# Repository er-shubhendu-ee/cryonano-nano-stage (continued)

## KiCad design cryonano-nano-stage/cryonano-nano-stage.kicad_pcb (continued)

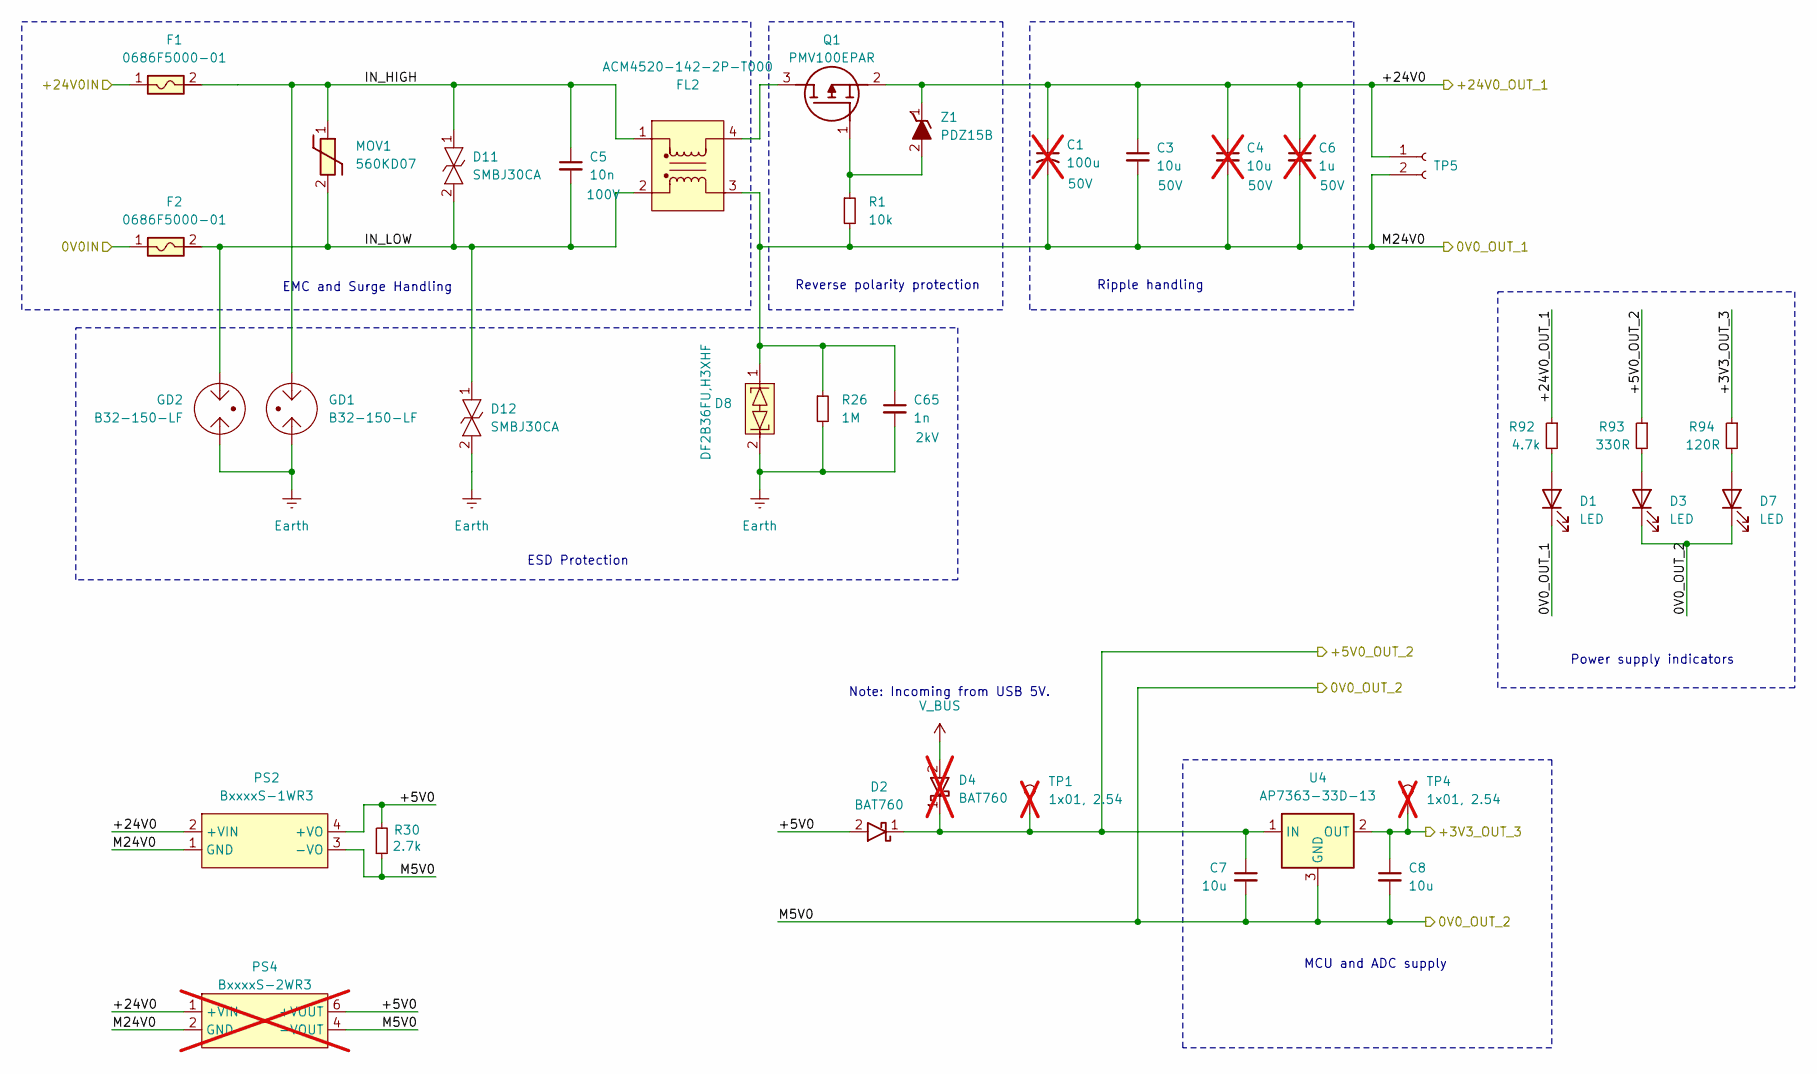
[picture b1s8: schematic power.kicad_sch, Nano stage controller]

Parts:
C1: 100u; CP_Radial_D8.0mm_P3.50mm; Voltage 50V; not fitted
C3: 10u; C_1210_3225Metric; Voltage 50V
C4: 10u; C_1210_3225Metric; Voltage 50V; not fitted
C5: 10n; C_1206_3216Metric; Voltage 100V
C6: 1u; C_0805_2012Metric; Voltage 50V; not fitted
C7, C8: 10u; C_1206_3216Metric; Voltage 16V
C65: 1n; C_Disc_D9.0mm_W5.0mm_P7.50mm; Voltage 2kV
D1, D3, D7: LED; LED_0603_1608Metric_Pad1.05x0.95mm_HandSolder
D2: BAT760; D_SOD-323; Voltage 30V
D4: BAT760; D_SOD-323; not fitted
D8: DF2B36FU,H3XHF; D_SOD-323
D11, D12: SMBJ30CA; D_SMB; Voltage 30V
F1, F2: 0686F5000-01; Fuse_0603_1608Metric
FL2: ACM4520-142-2P-T000; ACM45204212PT000
GD1, GD2: B32-150-LF; B32_GDT_YAGEO
MOV1: 560KD07; RV_Disc_D9mm_W4.8mm_P5mm
PS2: BxxxxS-1WR3
PS4: BxxxxS-2WR3; not fitted
Q1: PMV100EPAR; SOT95P230X110-3N
R1: 10k; R_0603_1608Metric
R26: 1M; R_Axial_DIN0207_L6.3mm_D2.5mm_P10.16mm_Horizontal
R30: 2.7k; R_0805_2012Metric
R92: 4.7k; R_0603_1608Metric
R93: 330R; R_0603_1608Metric
R94: 120R; R_0603_1608Metric
TP1, TP4: 1x01, 2.54; TestPoint_THTPad_D1.3mm_Drill0.8mm; not fitted
TP5: 1x02, 2.54; PinSocket_1x02_P2.54mm_Vertical
U4: AP7363-33D-13; TO252__DPAK__1
Z1: PDZ15B; SOD2512X110N

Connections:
/Block Diagram/+3V3: C8.1, R94.1, TP4.1 (1_1), U4.2 (OUT); also elsewhere on the board
/Block Diagram/+5V0: C7.1, D2.1 (K), D4.1 (K), R93.1, TP1.1 (1_1), U4.1 (IN); also elsewhere on the board
/Block Diagram/+24V0: C1.1, C3.1, C4.1, C6.1, PS2.2 (+VIN), PS4.1 (+VIN), Q1.2 (S), R92.1, TP5.1, Z1.1 (K); also elsewhere on the board
/Block Diagram/M24V0: C1.2, C3.2, C4.2, C6.2, C65.1, D1.1 (K), D8.1, FL2.3, PS2.1 (GND), PS4.2 (GND), R1.2, R26.1, TP5.2; also elsewhere on the board
/Block Diagram/Power/0V0IN: F2.1; also elsewhere on the board
/Block Diagram/Power/+5V0: D2.2 (A), PS2.4 (+VO), PS4.6 (+VOUT), R30.2
/Block Diagram/Power/+24V0IN: F1.1; also elsewhere on the board
/Block Diagram/Power/IN_HIGH: C5.1, D11.1, F1.2, FL2.1, GD1.1, MOV1.1
/Block Diagram/Power/IN_LOW: C5.2, D11.2, D12.1, F2.2, FL2.2, GD2.1, MOV1.2
Earth: C65.2, D8.2, D12.2, GD1.2, GD2.2, R26.2; also elsewhere on the board
GND: C7.2, C8.2, D3.1 (K), D7.1 (K), PS2.3 (-VO), PS4.4 (-VOUT), R30.1, U4.3 (GND); also elsewhere on the board
unnamed: D1.2 (A), R92.2
unnamed: D3.2 (A), R93.2
unnamed: D7.2 (A), R94.2
unnamed: FL2.4, Q1.3 (D)
unnamed: Q1.1 (G), R1.1, Z1.2 (A)
V_BUS: D4.2 (A); also elsewhere on the board

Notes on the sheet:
Power supply indicators
ESD Protection
EMC and Surge Handling
Reverse polarity protection
MCU and ADC supply
Ripple handling
Note: Incoming from USB 5V.

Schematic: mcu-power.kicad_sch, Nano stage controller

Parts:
C14: 4.7u; C_0805_2012Metric; Voltage 16V; Tolerence 10%
C15, C43, C44, C45, C46, C47, C48, C49, C50, C53, C55, C59: 100n; C_0603_1608Metric; Voltage 16V
C51, C52, C54: 1u; C_0603_1608Metric; Voltage 16V; Tolerence 10%
C56, C57: 2.2u; C_0603_1608Metric; Voltage 16V; Tolerence 10%
U7: STM32H753ZITx; LQFP-144_20x20mm_P0.5mm

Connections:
/Block Diagram/Controller/MCU Power/VCAP: C56.1, C57.1, U7.71 (VCAP), U7.106 (VCAP)
/Block Diagram/Controller/VDD: C14.1, C15.1, C43.1, C44.1, C45.1, C46.1, C47.1, C48.1, C49.1, C50.1, C51.1, C52.1, C53.1, C54.1, C55.1, C59.1, U7.6 (VBAT), U7.17 (VDD), U7.30 (VDD), U7.32 (VREF+), U7.33 (VDDA), U7.39 (VDD), U7.52 (VDD), U7.62 (VDD), U7.72 (VDD), U7.84 (VDD), U7.95 (VDD33_USB), U7.108 (VDD), U7.121 (VDD), U7.131 (VDD), U7.144 (VDD); also elsewhere on the board
GND: C14.2, C15.2, C43.2, C44.2, C45.2, C46.2, C47.2, C48.2, C49.2, C50.2, C51.2, C52.2, C53.2, C54.2, C55.2, C56.2, C57.2, C59.2, U7.16 (VSS), U7.31 (VSSA), U7.38 (VSS), U7.51 (VSS), U7.61 (VSS), U7.83 (VSS), U7.94 (VSS), U7.107 (VSS), U7.120 (VSS), U7.130 (VSS); also elsewhere on the board

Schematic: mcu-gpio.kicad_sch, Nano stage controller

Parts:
C16: 100n; C_0603_1608Metric; Voltage 16V; not fitted
C17: 100n; C_0603_1608Metric; Voltage 16V
C33, C34: 33pF; C_0603_1608Metric; Voltage 16V; not fitted
C36, C37: 8p; C_0603_1608Metric; Voltage 16V; not fitted
D6: ESDB3V3C-AQ; SOT-23
R35: 470R; R_0603_1608Metric
R36, R38: 10k; R_0603_1608Metric
R68, R86: 10k; R_0603_1608Metric; not fitted
SW1: BOOT; SW_PUSH_6mm
SW2: RESET; SW_PUSH_6mm
TP2: 1x01, 2.54; TestPoint_THTPad_D1.3mm_Drill0.8mm; not fitted
TP3: 1x02, 2.54; PinSocket_1x02_P2.54mm_Vertical
U7: STM32H753ZITx; LQFP-144_20x20mm_P0.5mm
Y1: 12MHz; Crystal_SMD_2520-4Pin_2.5x2.0mm
Y2: 32.768kHz; Crystal_SMD_3215-2Pin_3.2x1.5mm; not fitted

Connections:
/Block Diagram/ADC/CLK: U7.99 (PC9); also elsewhere on the board
/Block Diagram/ADC/DIN: U7.67 (PE14); also elsewhere on the board
/Block Diagram/ADC/DOUT/~RDY: U7.63 (PE10), U7.66 (PE13); also elsewhere on the board
/Block Diagram/ADC/SCLK: U7.65 (PE12); also elsewhere on the board
/Block Diagram/ADC/~CS: U7.64 (PE11); also elsewhere on the board
/Block Diagram/ADC/~SYNC: U7.68 (PE15); also elsewhere on the board
/Block Diagram/Communication/RMII_CRS_DV: U7.43 (PA7); also elsewhere on the board
/Block Diagram/Communication/RMII_MDC: U7.27 (PC1); also elsewhere on the board
/Block Diagram/Communication/RMII_MDIO: U7.36 (PA2); also elsewhere on the board
/Block Diagram/Communication/RMII_REF_CLK: U7.35 (PA1); also elsewhere on the board
/Block Diagram/Communication/RMII_RXD0: U7.44 (PC4); also elsewhere on the board
/Block Diagram/Communication/RMII_RXD1: U7.45 (PC5); also elsewhere on the board
/Block Diagram/Communication/RMII_TXD0: U7.73 (PB12); also elsewhere on the board
/Block Diagram/Communication/RMII_TXD1: U7.74 (PB13); also elsewhere on the board
/Block Diagram/Communication/RMII_TX_EN: U7.70 (PB11); also elsewhere on the board
/Block Diagram/Communication/USB_D+: U7.104 (PA12); also elsewhere on the board
/Block Diagram/Communication/USB_D-: U7.103 (PA11); also elsewhere on the board
/Block Diagram/Communication/USB_VBUS: R68.1; also elsewhere on the board
/Block Diagram/Controller/LOG_RX: U7.112 (PC11); also elsewhere on the board
/Block Diagram/Controller/LOG_TX: U7.111 (PC10); also elsewhere on the board
/Block Diagram/Controller/MCU GPIO/BOOT0: C16.1, D6.2 (SIG2), R36.1, SW1.1, U7.138 (BOOT0)
/Block Diagram/Controller/MCU GPIO/PDR_ON: R38.2, R86.1, U7.143 (PDR_ON)
/Block Diagram/Controller/MCU GPIO/RCC_OSC32_IN: C36.1, U7.8 (PC14), Y2.2
/Block Diagram/Controller/MCU GPIO/RCC_OSC32_OUT: C37.1, U7.9 (PC15), Y2.1
/Block Diagram/Controller/MCU GPIO/RCC_OSC_IN: C33.1, U7.23 (PH0), Y1.3
/Block Diagram/Controller/MCU GPIO/RCC_OSC_OUT: C34.1, U7.24 (PH1), Y1.1
/Block Diagram/Controller/MCU GPIO/SCL: TP3.1, U7.136 (PB6)
/Block Diagram/Controller/MCU GPIO/SDA: TP3.2, U7.137 (PB7)
/Block Diagram/Controller/MCU GPIO/USB_ID: U7.102 (PA10)
/Block Diagram/Controller/NRST: C17.1, D6.1 (SIG1), SW2.1, U7.25 (NRST); also elsewhere on the board
/Block Diagram/Controller/PWMOUT: U7.60 (PE9); also elsewhere on the board
/Block Diagram/Controller/SWCLK: U7.109 (PA14); also elsewhere on the board
/Block Diagram/Controller/SWDIO: U7.105 (PA13); also elsewhere on the board
/Block Diagram/Controller/SWO: U7.133 (PB3); also elsewhere on the board
/Block Diagram/Controller/VDD: R35.1, R38.1; also elsewhere on the board
GND: C16.2, C17.2, C33.2, C34.2, C36.2, C37.2, D6.3 (COM), R36.2, R86.2, SW2.2, Y1.2 (G), Y1.4 (G); also elsewhere on the board
unnamed: R35.2, SW1.2
unnamed: TP2.1 (1_1), U7.100 (PA8)
unnamed: R68.2, U7.101 (PA9)

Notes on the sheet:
ESD
RESET
BOOT memory selection.

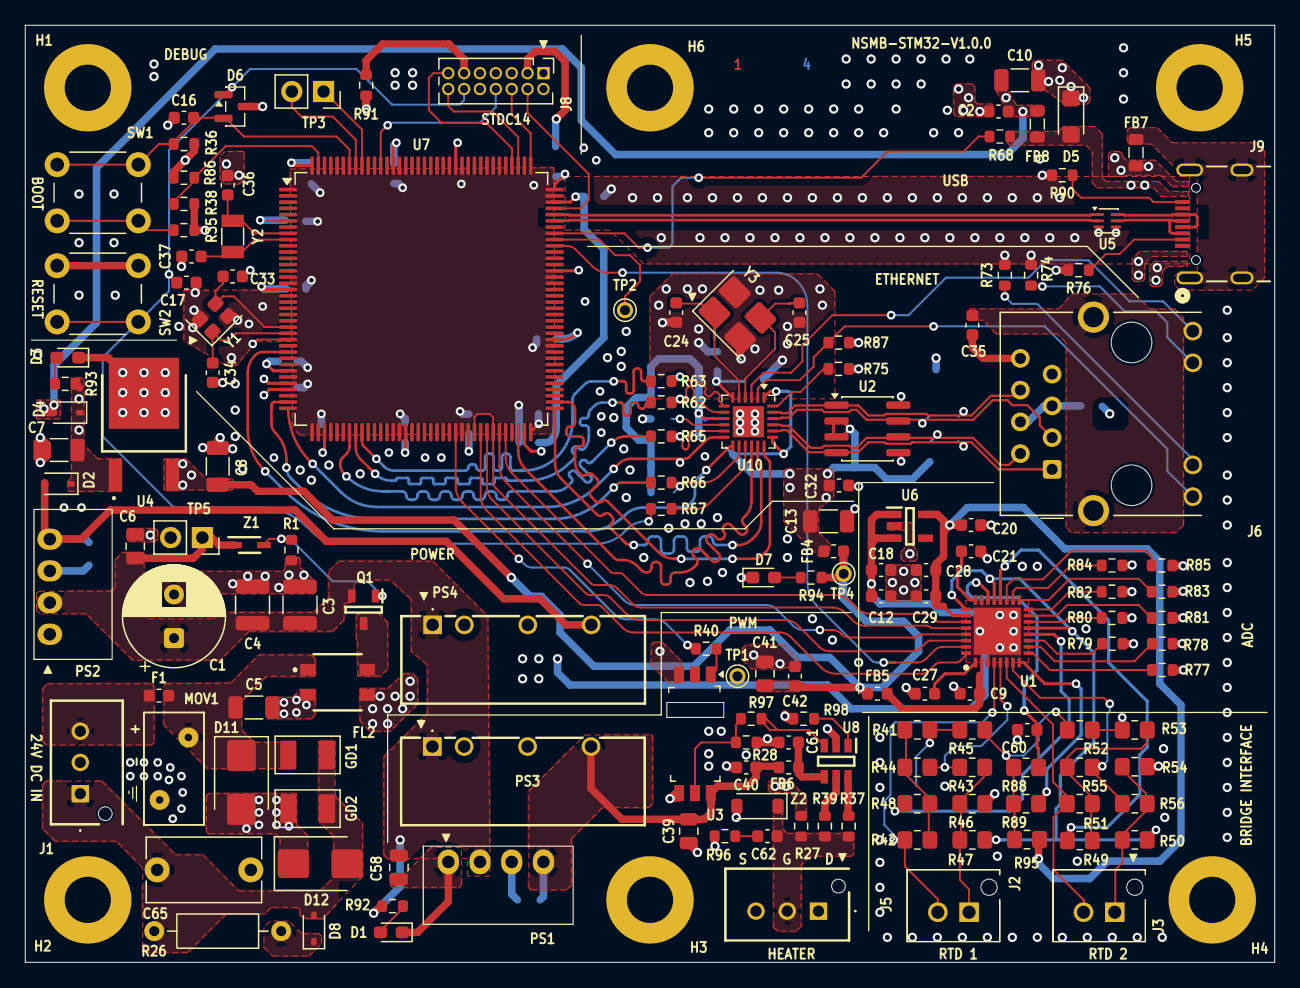
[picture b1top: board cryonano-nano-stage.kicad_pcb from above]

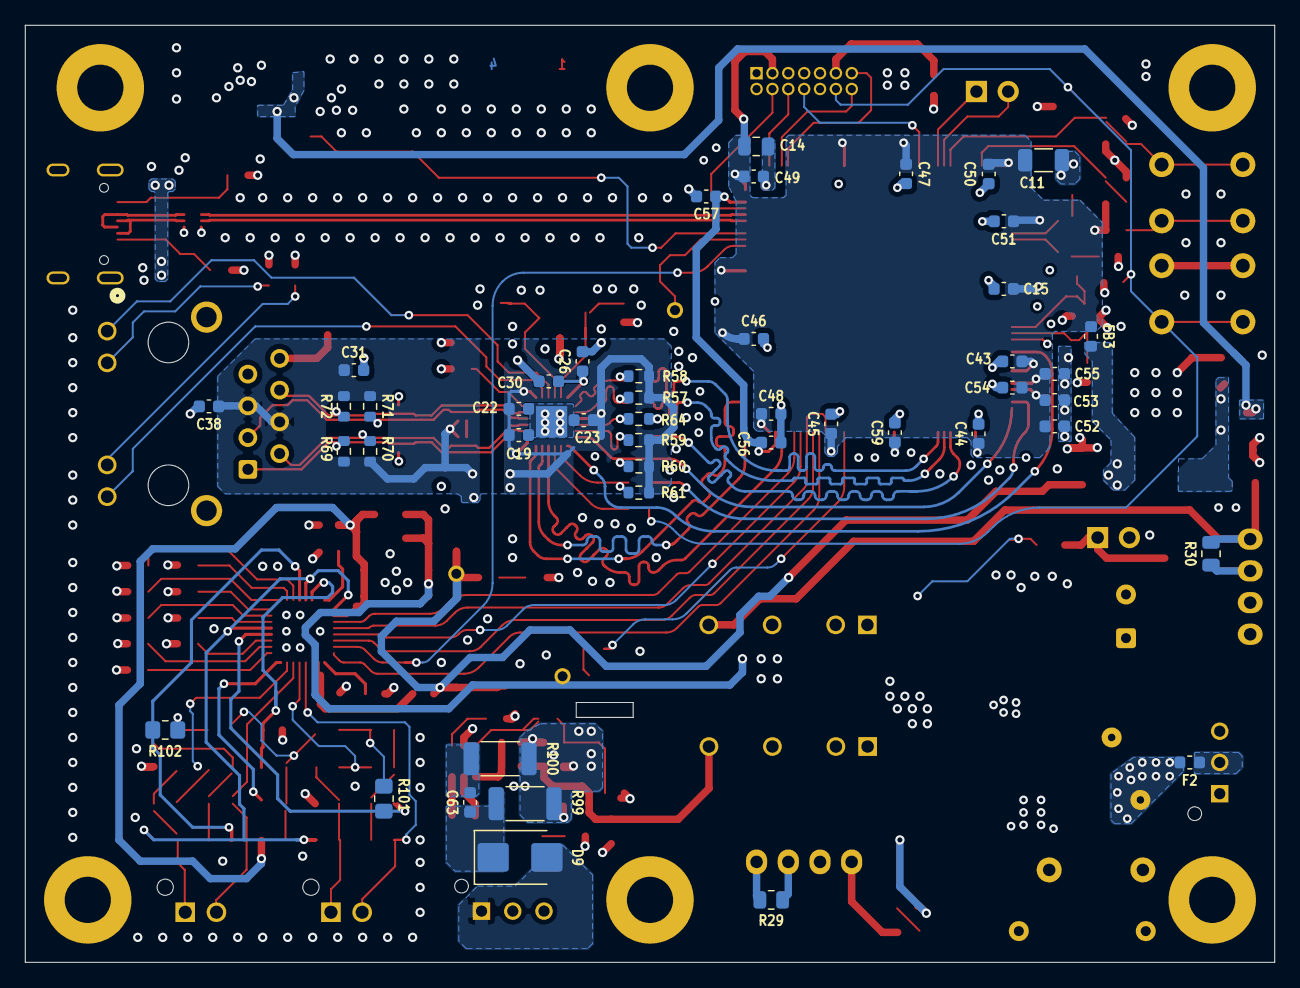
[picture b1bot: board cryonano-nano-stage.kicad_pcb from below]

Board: 4 copper layers, 100.0 x 75.0 mm, 200 parts (46 on the bottom side), 125 nets.
